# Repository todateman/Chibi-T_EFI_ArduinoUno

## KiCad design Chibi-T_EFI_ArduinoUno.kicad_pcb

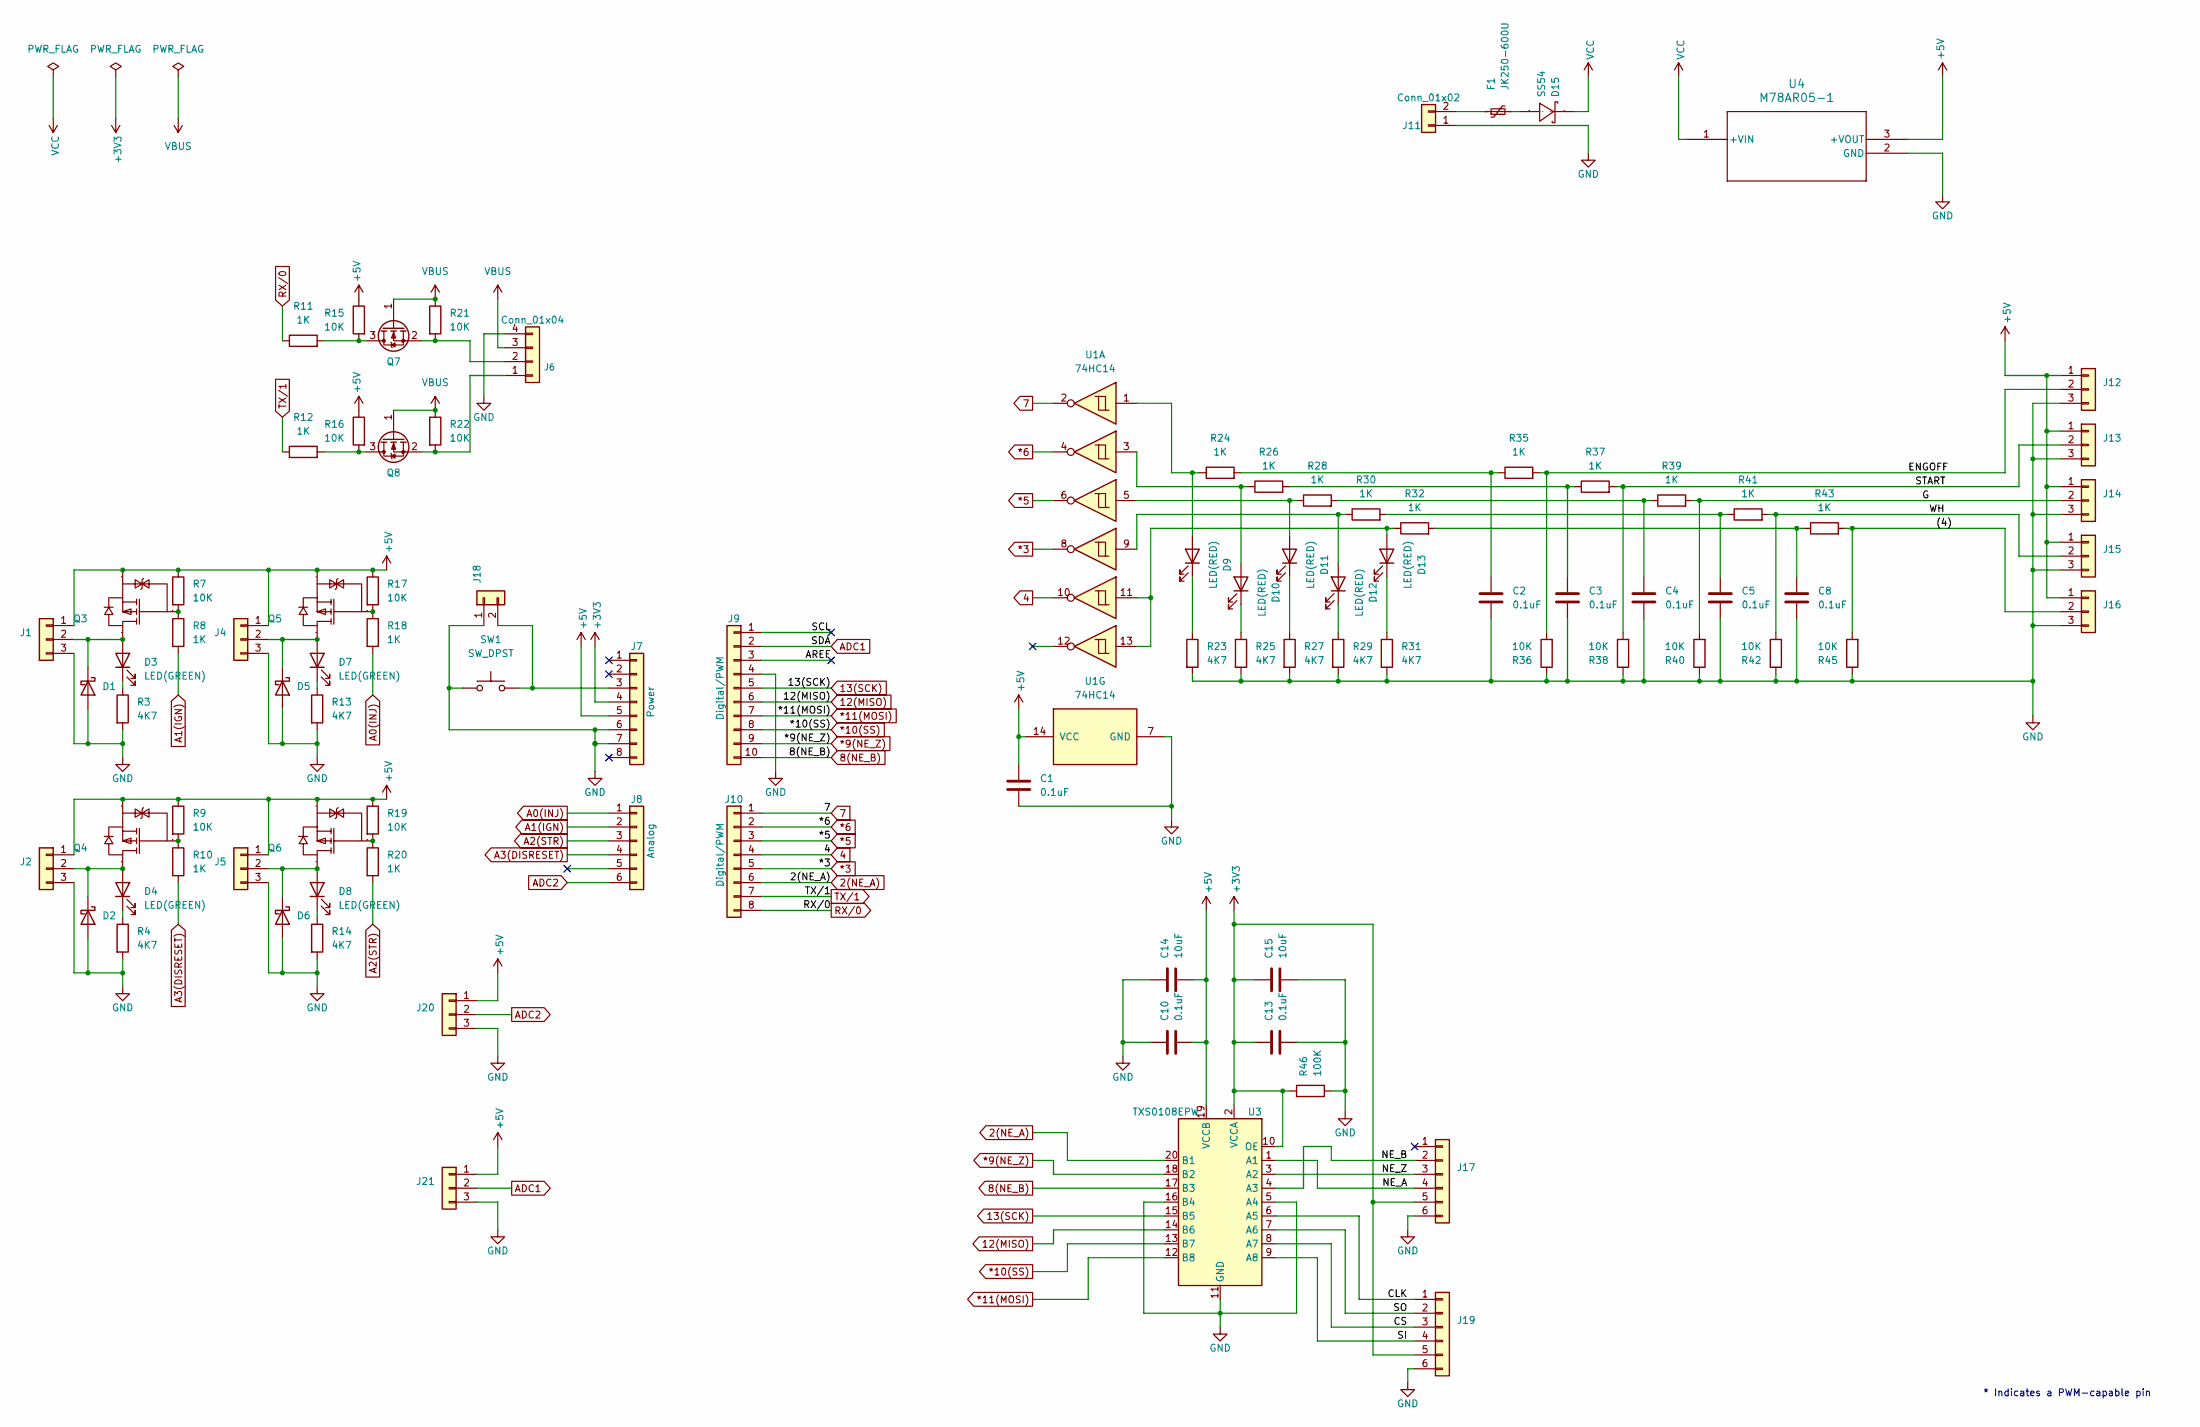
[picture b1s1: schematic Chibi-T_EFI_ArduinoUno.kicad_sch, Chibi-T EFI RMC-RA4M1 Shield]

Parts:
C1, C2, C3, C4, C5, C8, C10, C13: 0.1uF; C_0603_1608Metric; LCSC C14663
C14, C15: 10uF; C_0603_1608Metric; LCSC C19702
D1, D2, D5, D6: 40V 550mV@2A 2A SOD-123FL Schottky Barrier Diodes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; D_SOD-123F; LCSC C489144
D3, D4, D7, D8: LED(GREEN); LED_0603_1608Metric; LCSC C22371297
D9, D10, D11, D12, D13: LED(RED); LED_0603_1608Metric; LCSC C2286
D15: SS54; SMA_L4.4-W2.8-LS5.4-R-RD; Manufacturer Part SS54; LCSC C22452
F1: JK250-600U; Fuse_Bourns_MF-RHT600; LCSC C369135
J1, J2, J4, J5, J12, J13, J14, J15, J16, J20: Conn_01x03; JST_EH_B3B-EH-A_1x03_P2.50mm_Vertical; LCSC C398546
J6: Conn_01x04; JST_EH_B4B-EH-A_1x04_P2.50mm_Vertical; LCSC C265288
J7: Power; PinSocket_1x08_P2.54mm_Vertical
J8: Analog; PinSocket_1x06_P2.54mm_Vertical
J9: Digital/PWM; PinSocket_1x10_P2.54mm_Vertical
J10: Digital/PWM; PinSocket_1x08_P2.54mm_Vertical
J11: Conn_01x02; AMASS_XT30UPB-M_1x02_P5.0mm_Vertical; LCSC C428721
J17, J19: Conn_01x06; JST_EH_B6B-EH-A_1x06_P2.50mm_Vertical; LCSC C160255
J18: Conn_01x03; JST_EH_B2B-EH-A_1x02_P2.50mm_Vertical; LCSC C160262
J21: Conn_01x03; PinHeader_1x03_P2.54mm_Vertical
Q3, Q4, Q5, Q6: DMP32D4S-13; SOT-323-3_L2.0-W1.3-P1.30-LS2.1-BR; Manufacturer Part DMP32D4SW-7; LCSC C461086
Q7, Q8: BSS138; SOT-23; LCSC C5224260
R3, R4, R13, R14, R23, R25, R27, R29, R31: 4K7; R_0603_1608Metric; LCSC C23162
R7, R9, R15, R16, R17, R19, R21, R22, R36, R38, R40, R42, R45: 10K; R_0603_1608Metric; LCSC C25804
R8, R10, R11, R12, R18, R20, R24, R26, R28, R30, R32, R35, R37, R39, R41, R43: 1K; R_0603_1608Metric; LCSC C21190
R46: 100K; R_0603_1608Metric; LCSC C25803
SW1: SW_DPST; SW_Tactile_SPST_NO_Straight_CK_PTS636Sx25SMTRLFS; LCSC C2689642
U1: 74HC14; SOIC-14_3.9x8.7mm_P1.27mm; LCSC C5605
U3: TXS0108EPW; TSSOP-20_4.4x6.5mm_P0.65mm; LCSC C17206
U4: M78AR05-1; SIP3_M78AR-0.5_MIN; LCSC C9900088842

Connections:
2(NE_A): J10.6, U3.20 (B1)
4: J10.4, U1.10
7: J10.1, U1.2
8(NE_B): J9.10, U3.17 (B3)
12(MISO): J9.6, U3.14 (B6)
13(SCK): J9.5, U3.15 (B5)
*3: J10.5, U1.8
*5: J10.3, U1.6
*6: J10.2, U1.4
*9(NE_Z): J9.9, U3.18 (B2)
*10(SS): J9.8, U3.13 (B7)
*11(MOSI): J9.7, U3.12 (B8)
+3V3: C13.1, C15.1, J7.4, J17.5, J19.5, R46.1, U3.2 (VCCA), U3.10 (OE)
+5V: C1.1, C10.2, C14.2, J1.1, J2.1, J4.1, J5.1, J7.5, J12.1, J13.1, J14.1, J15.1, J16.1, J20.1, J21.1, Q3.2 (S), Q4.2 (S), Q5.2 (S), Q6.2 (S), R7.1, R9.1, R15.1, R16.1, R17.1, R19.1, U1.14 (VCC), U3.19 (VCCB), U4.3 (+VOUT)
/(4): J16.2, R43.2, R45.2
/AREF: J9.3
/CLK: J19.1, U3.6 (A5)
/CS: J19.3, U3.8 (A7)
/ENGOFF: J12.2, R35.2, R36.2
/G: J14.2, R39.2, R40.2
/NE_A: J17.4, U3.1 (A1)
/NE_B: J17.2, U3.4 (A3)
/NE_Z: J17.3, U3.3 (A2)
/SCL: J9.1
/SI: J19.4, U3.9 (A8)
/SO: J19.2, U3.7 (A6)
/START: J13.2, R37.2, R38.2
/WH: J15.2, R41.2, R42.2
A0(INJ): J8.1, R18.2
A1(IGN): J8.2, R8.2
A2(STR): J8.3, R20.2
A3(DISRESET): J8.4, R10.2
ADC1: J9.2, J21.2
ADC2: J8.6, J20.2
GND: C1.2, C2.2, C3.2, C4.2, C5.2, C8.2, C10.1, C13.2, C14.1, C15.2, D1.2 (A), D2.2 (A), D5.2 (A), D6.2 (A), J1.3, J2.3, J4.3, J5.3, J6.4, J7.6, J7.7, J9.4, J11.1, J12.3, J13.3, J14.3, J15.3, J16.3, J17.6, J18.1, J19.6, J20.3, J21.3, R3.2, R4.2, R13.2, R14.2, R23.2, R25.2, R27.2, R29.2, R31.2, R36.1, R38.1, R40.1, R42.1, R45.1, R46.2, SW1.1, U1.7 (GND), U3.5 (A4), U3.11 (GND), U3.16 (B4), U4.2 (GND)
unnamed: C2.1, R24.2, R35.1
unnamed: C3.1, R26.2, R37.1
unnamed: C4.1, R28.2, R39.1
unnamed: C5.1, R30.2, R41.1
unnamed: C8.1, R32.2, R43.1
unnamed: D1.1 (K), D3.2 (A), J1.2, Q3.3 (D)
unnamed: D2.1 (K), D4.2 (A), J2.2, Q4.3 (D)
unnamed: D3.1 (K), R3.1
unnamed: D4.1 (K), R4.1
unnamed: D5.1 (K), D7.2 (A), J4.2, Q5.3 (D)
unnamed: D6.1 (K), D8.2 (A), J5.2, Q6.3 (D)
unnamed: D7.1 (K), R13.1
unnamed: D8.1 (K), R14.1
unnamed: D9.2 (A), R24.1, U1.1
unnamed: D9.1 (K), R23.1
unnamed: D10.2 (A), R26.1, U1.3
unnamed: D10.1 (K), R25.1
unnamed: D11.2 (A), R28.1, U1.5
unnamed: D11.1 (K), R27.1
unnamed: D12.2 (A), R30.1, U1.9
unnamed: D12.1 (K), R29.1
unnamed: D13.2 (A), R32.1, U1.11, U1.13
unnamed: D13.1 (K), R31.1
unnamed: D15.1 (A), F1.2
unnamed: J6.1, Q8.2 (S), R22.2
unnamed: J6.2, Q7.2 (S), R21.2
unnamed: F1.1, J11.2
unnamed: J7.3, J18.2, SW1.2
unnamed: Q3.1 (G), R7.2, R8.1
unnamed: Q4.1 (G), R9.2, R10.1
unnamed: Q5.1 (G), R17.2, R18.1
unnamed: Q6.1 (G), R19.2, R20.1
unnamed: Q7.3 (D), R11.2, R15.2
unnamed: Q8.3 (D), R12.2, R16.2
RX/0: J10.8, R11.1
TX/1: J10.7, R12.1
VBUS: J6.3, Q7.1 (G), Q8.1 (G), R21.1, R22.1
VCC: D15.2 (K), U4.1 (+VIN)

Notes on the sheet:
* Indicates a PWM-capable pin

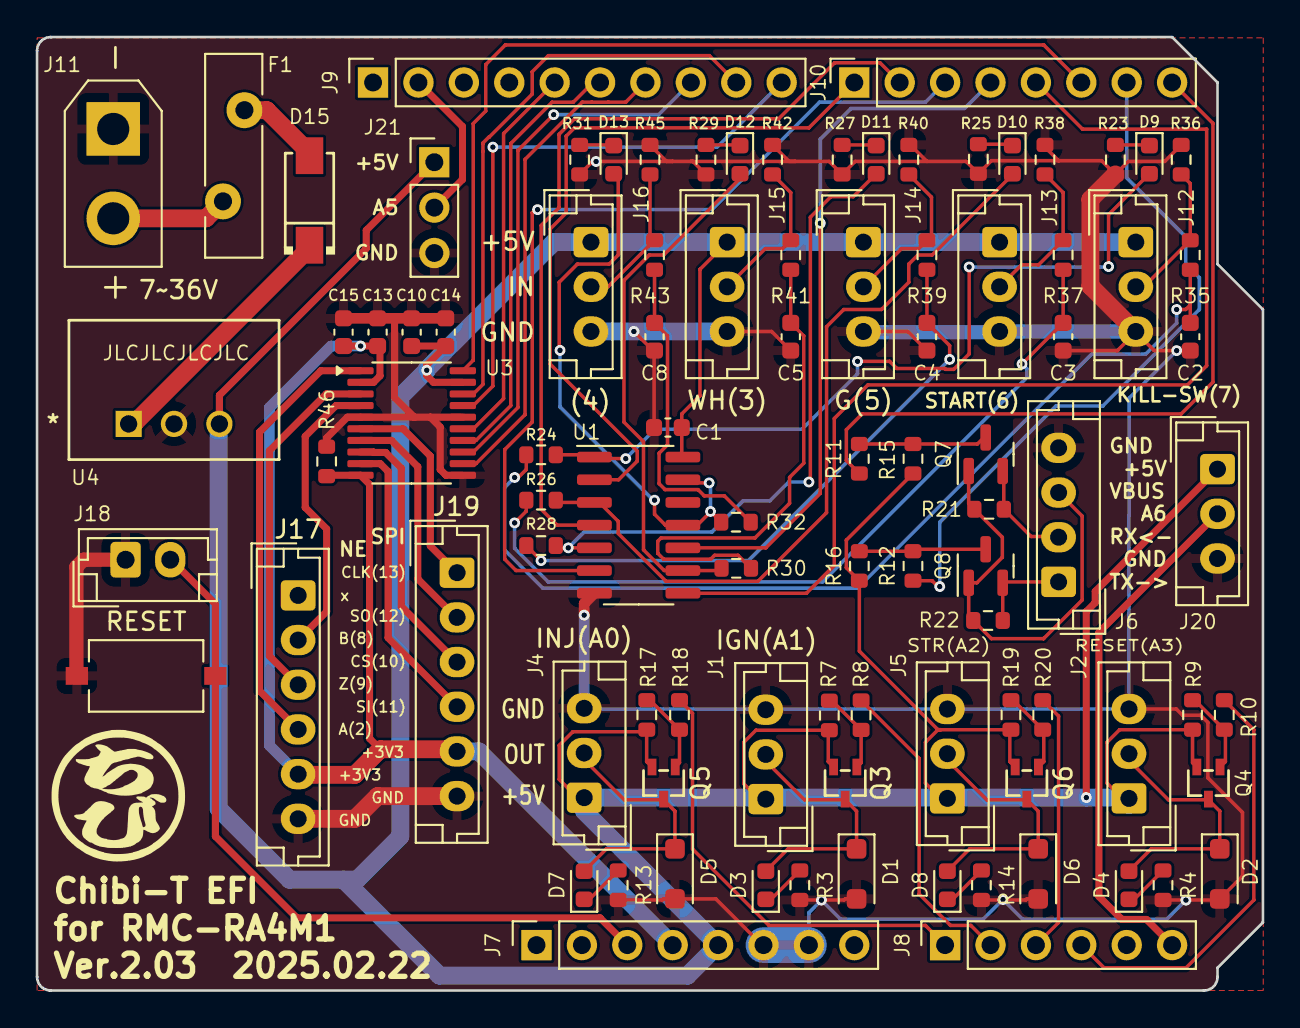
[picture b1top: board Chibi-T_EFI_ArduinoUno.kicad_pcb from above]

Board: 2 copper layers, 68.6 x 53.3 mm, 94 parts (0 on the bottom side), 71 nets.

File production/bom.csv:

Designator,Footprint,Quantity,Value,LCSC Part #
"C1, C10, C13, C2, C3, C4, C5, C8",0603,8,0.1uF,C14663
"C14, C15",0603,2,10uF,C19702
"D1, D2, D5, D6",D_SOD-123F,4,40V 550mV@2A 2A SOD-123FL Schottky Barrier Diodes (SBD) ROHS,C489144
"D10, D11, D12, D13, D9",0603,5,LED(RED),C2286
D15,SMA_L4.4-W2.8-LS5.4-R-RD,1,SS54,C22452
"D3, D4, D7, D8",0603,4,LED(GREEN),C22371297
F1,Fuse_Bourns_MF-RHT600,1,JK250-600U,C369135
"J1, J12, J13, J14, J15, J16, J2, J20, J4, J5",JST_EH_B3B-EH-A_1x03_P2.50mm_Vertical,10,Conn_01x03,C398546
J11,AMASS_XT30UPB-M_1x02_P5.0mm_Vertical,1,Conn_01x02,C428721
"J17, J19",JST_EH_B6B-EH-A_1x06_P2.50mm_Vertical,2,Conn_01x06,C160255
J18,JST_EH_B2B-EH-A_1x02_P2.50mm_Vertical,1,Conn_01x03,C160262
J6,JST_EH_B4B-EH-A_1x04_P2.50mm_Vertical,1,Conn_01x04,C265288
"Q3, Q4, Q5, Q6",SOT-323-3_L2.0-W1.3-P1.30-LS2.1-BR,4,DMP32D4S-13,C461086
"Q7, Q8",SOT-23,2,BSS138,C5224260
"R10, R11, R12, R18, R20, R24, R26, R28, R30, R32, R35, R37, R39, R41, R43, R8",0603,16,1K,C21190
"R13, R14, R23, R25, R27, R29, R3, R31, R4",0603,9,4K7,C23162
"R15, R16, R17, R19, R21, R22, R36, R38, R40, R42, R45, R7, R9",0603,13,10K,C25804
R46,0603,1,100K, C25803
SW1,SW_Tactile_SPST_NO_Straight_CK_PTS636Sx25SMTRLFS,1,SW_DPST,C2689642
U1,SOIC-14_3.9x8.7mm_P1.27mm,1,74HC14,C5605
U3,TSSOP-20_4.4x6.5mm_P0.65mm,1,TXS0108EPW, C17206

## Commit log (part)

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2024-12-31 RMC-RA4M1に合わせて回路図を修正
2024-12-31 NE-A,-Zの端子を追加、Resetの端子を変更
2024-12-31 基板レイアウトを修正
2024-12-31 SS54をLCSCのモデルに修正
2024-12-31 GREEN LEDの品番を在庫品に変更
2024-12-31 Grove端子とBSS138にLCSC品番を追加
2024-12-31 回路図のpdfを出力
2024-12-31 ピン配列を変更。回路図をpdfで出力
2025-01-01 クランク角エンコーダの端子を変更
2025-01-01 クランク角エンコーダ信号にレベル変換を追加
2025-01-01 インダクタのフットプリントを修正
2025-01-13 電源周辺のレイアウトを修正・サーマルパッドを追加
2025-01-13 ArduinoのVinへの+5Vを削除
2025-02-22 DCDCコンバータをパッケージ化 SPI・ADC用コネクタを追加
2025-02-22 ADC用端子を修正 JLCPCBに在庫のない部品を見直し
